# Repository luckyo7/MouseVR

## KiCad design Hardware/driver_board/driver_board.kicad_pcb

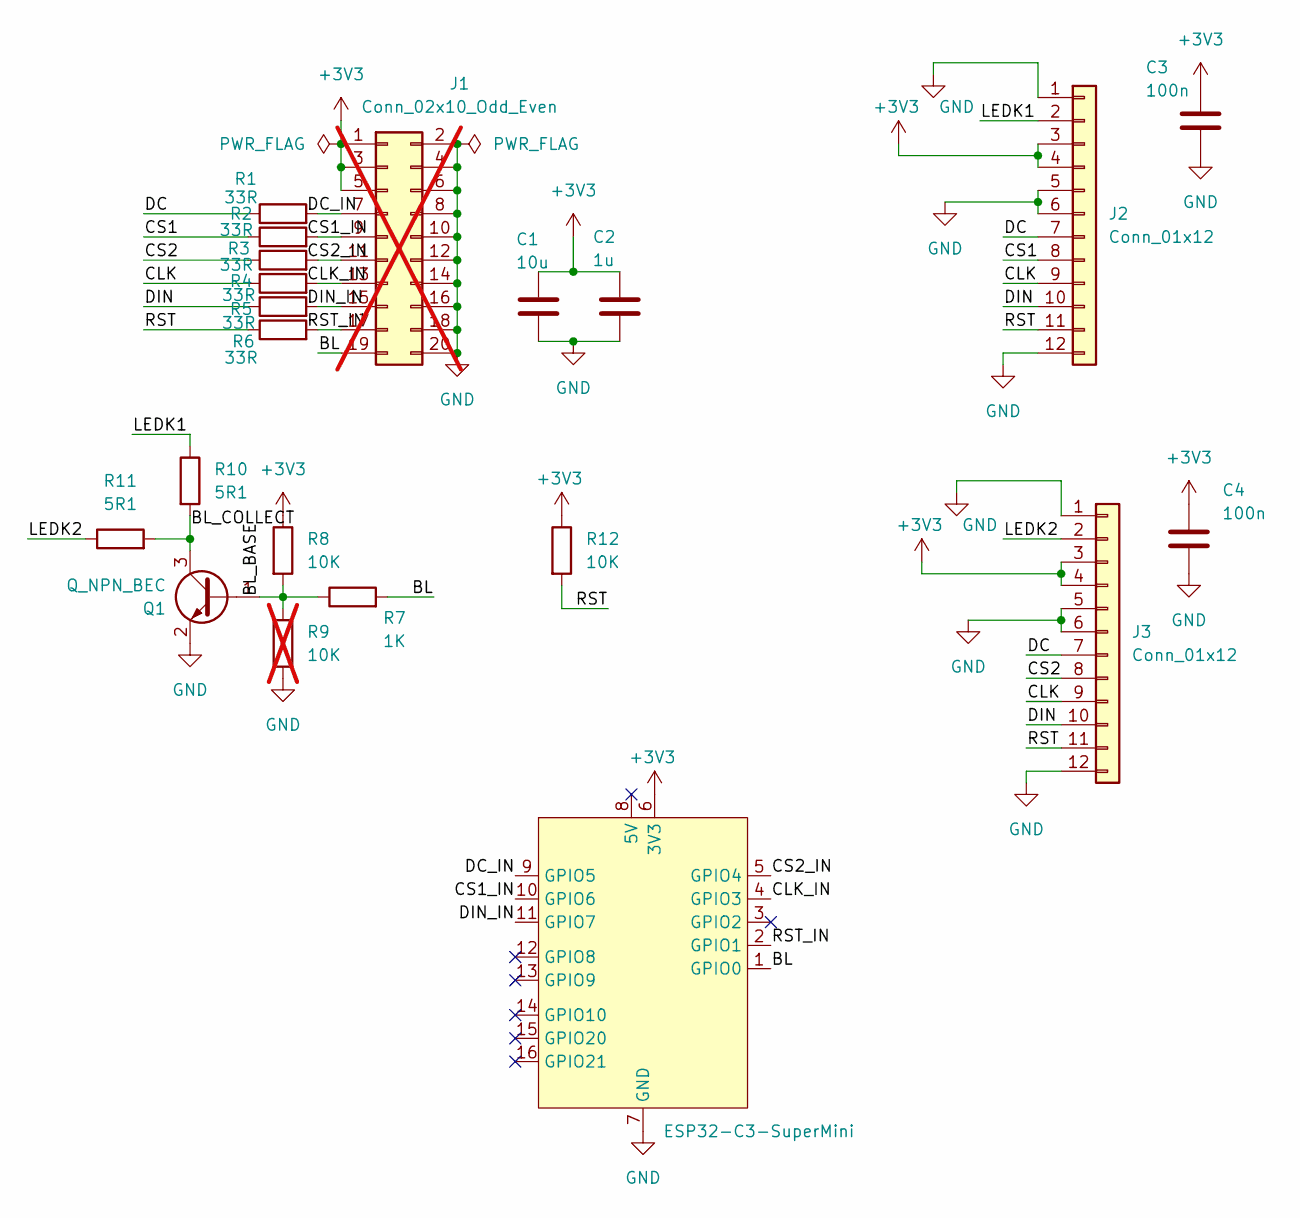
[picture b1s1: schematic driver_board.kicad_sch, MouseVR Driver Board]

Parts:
C1: 10u; C_0805_2012Metric
C2: 1u; C_0603_1608Metric
C3, C4: 100n; C_0603_1608Metric
J1: Conn_02x10_Odd_Even; PinHeader_2x10_P2.54mm_Vertical; not fitted
J2, J3: Conn_01x12; Hirose_FH12-12S-0.5SH_1x12-1MP_P0.50mm_Horizontal
Q1: Q_NPN_BEC; SOT-23
R1, R2, R3, R4, R5, R6: 33R; R_0603_1608Metric
R7: 1K; R_0603_1608Metric
R8, R12: 10K; R_0603_1608Metric
R9: 10K; R_0603_1608Metric; not fitted
R10, R11: 5R1; R_0603_1608Metric
U1: ESP32-C3-SuperMini

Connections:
+3V3: C1.1, C2.1, C3.1, C4.1, J1.1, J1.3, J1.5, J2.3, J2.4, J3.3, J3.4, R8.1, R12.1, U1.6 (3V3)
/BL: J1.19, R7.2, U1.1 (GPIO0)
/BL_BASE: Q1.1 (B), R7.1, R8.2, R9.1
/BL_COLLECT: Q1.3 (C), R10.2, R11.2
/CLK: J2.9, J3.9, R4.1
/CS1: J2.8, R2.1
/CS2: J3.8, R3.1
/DC: J2.7, J3.7, R1.1
/DIN: J2.10, J3.10, R5.1
/LEDK1: J2.2, R10.1
/LEDK2: J3.2, R11.1
/RST: J2.11, J3.11, R6.1, R12.2
GND: C1.2, C2.2, C3.2, C4.2, J1.2, J1.4, J1.6, J1.8, J1.10, J1.12, J1.14, J1.16, J1.18, J1.20, J2.1, J2.5, J2.6, J2.12, J2.MP, J3.1, J3.5, J3.6, J3.12, J3.MP, Q1.2 (E), R9.2, U1.7 (GND)
unnamed: J1.7, R1.2
unnamed: J1.9, R2.2
unnamed: J1.11, R3.2
unnamed: J1.13, R4.2
unnamed: J1.15, R5.2
unnamed: J1.17, R6.2

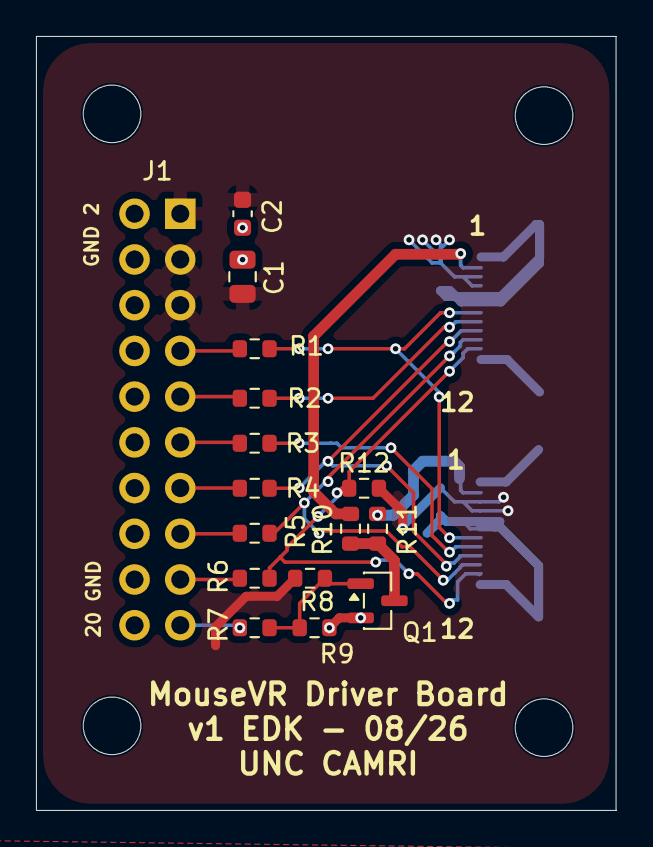
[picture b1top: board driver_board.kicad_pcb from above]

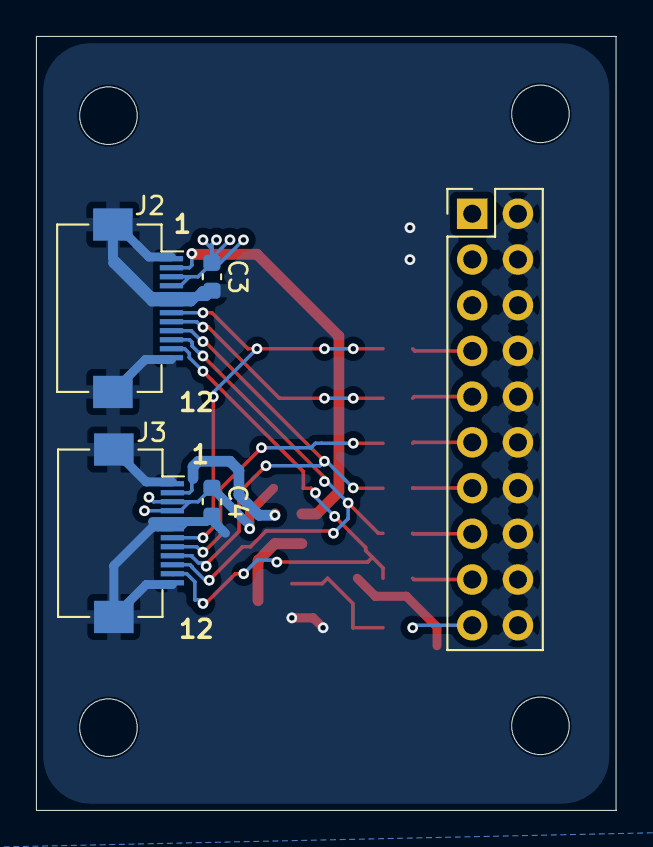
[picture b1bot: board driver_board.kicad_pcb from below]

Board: 2 copper layers, 32.2 x 43.0 mm, 20 parts (5 on the bottom side), 19 nets.

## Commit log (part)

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2026-06-25 init
